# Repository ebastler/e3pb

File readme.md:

# Ender 3 (Pro) Printbed

This is an attempt of uniting print surface and heating element into a single PCB. Both heating traces and temperature sensing are located on the bottom of the PCB, while the top surface is exposed FR4 (no copper, no soldermask). 

A LED on top indicates when the heatbed is being active. Temperature sensing uses a JST XH 2-pin connector, while the heating wires can either be directly soldered, or connected with a Amass XT30U connector. Target operating voltage/power: 24V 240W.

This is a WIP and shouldn't be used just yet - I am still waiting for my Ender 3 Pro to arrive to finalize the design and order protos.

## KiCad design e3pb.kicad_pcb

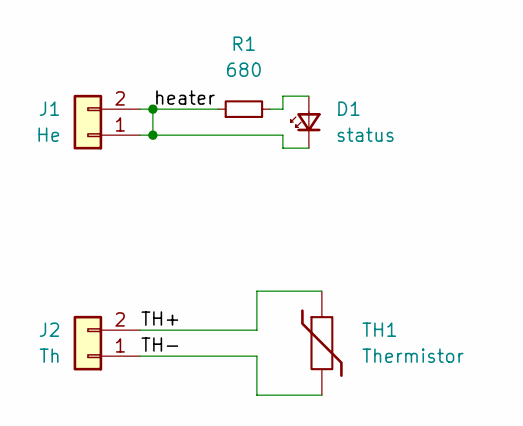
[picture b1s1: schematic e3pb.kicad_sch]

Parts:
D1: status; LED_0603_1608Metric_Pad1.05x0.95mm_HandSolder
J1: He; AMASS_XT30PW-M_1x02_P2.50mm_Horizontal
J2: Th; JST_XH_S2B-XH-A_1x02_P2.50mm_Horizontal
R1: 680; R_0603_1608Metric_Pad0.98x0.95mm_HandSolder
TH1: Thermistor; R_0603_1608Metric_Pad0.98x0.95mm_HandSolder

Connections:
/TH+: J2.2, TH1.1
/TH-: J2.1, TH1.2
/heater: D1.1 (K), J1.1, J1.2, R1.1
unnamed: D1.2 (A), R1.2

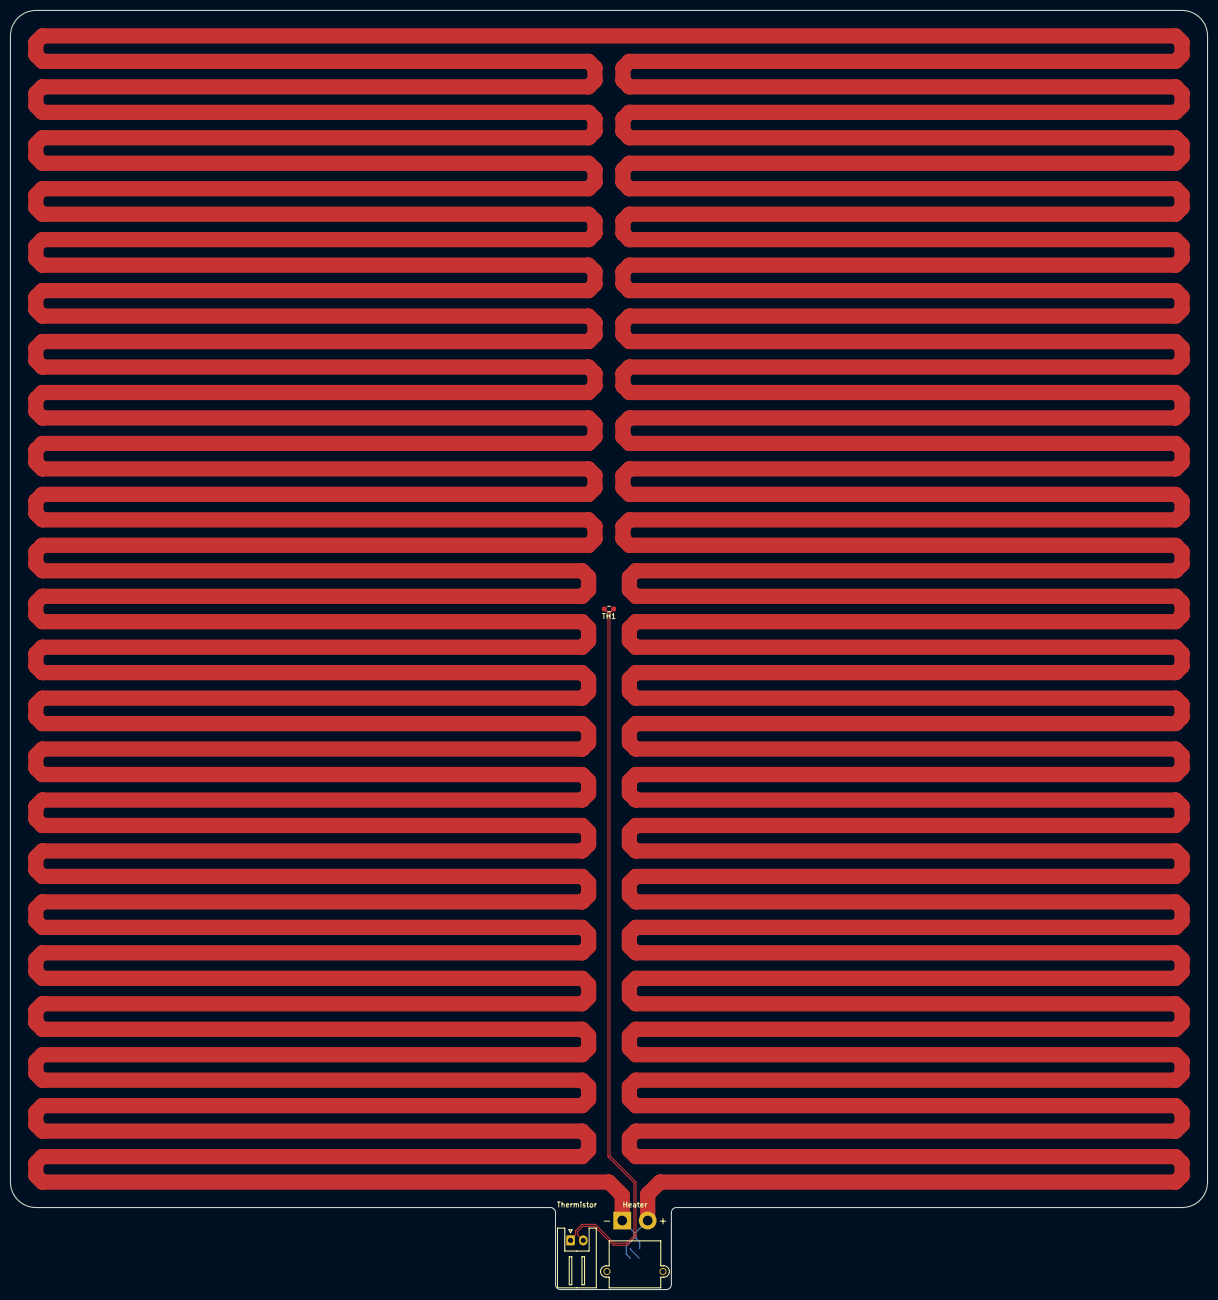
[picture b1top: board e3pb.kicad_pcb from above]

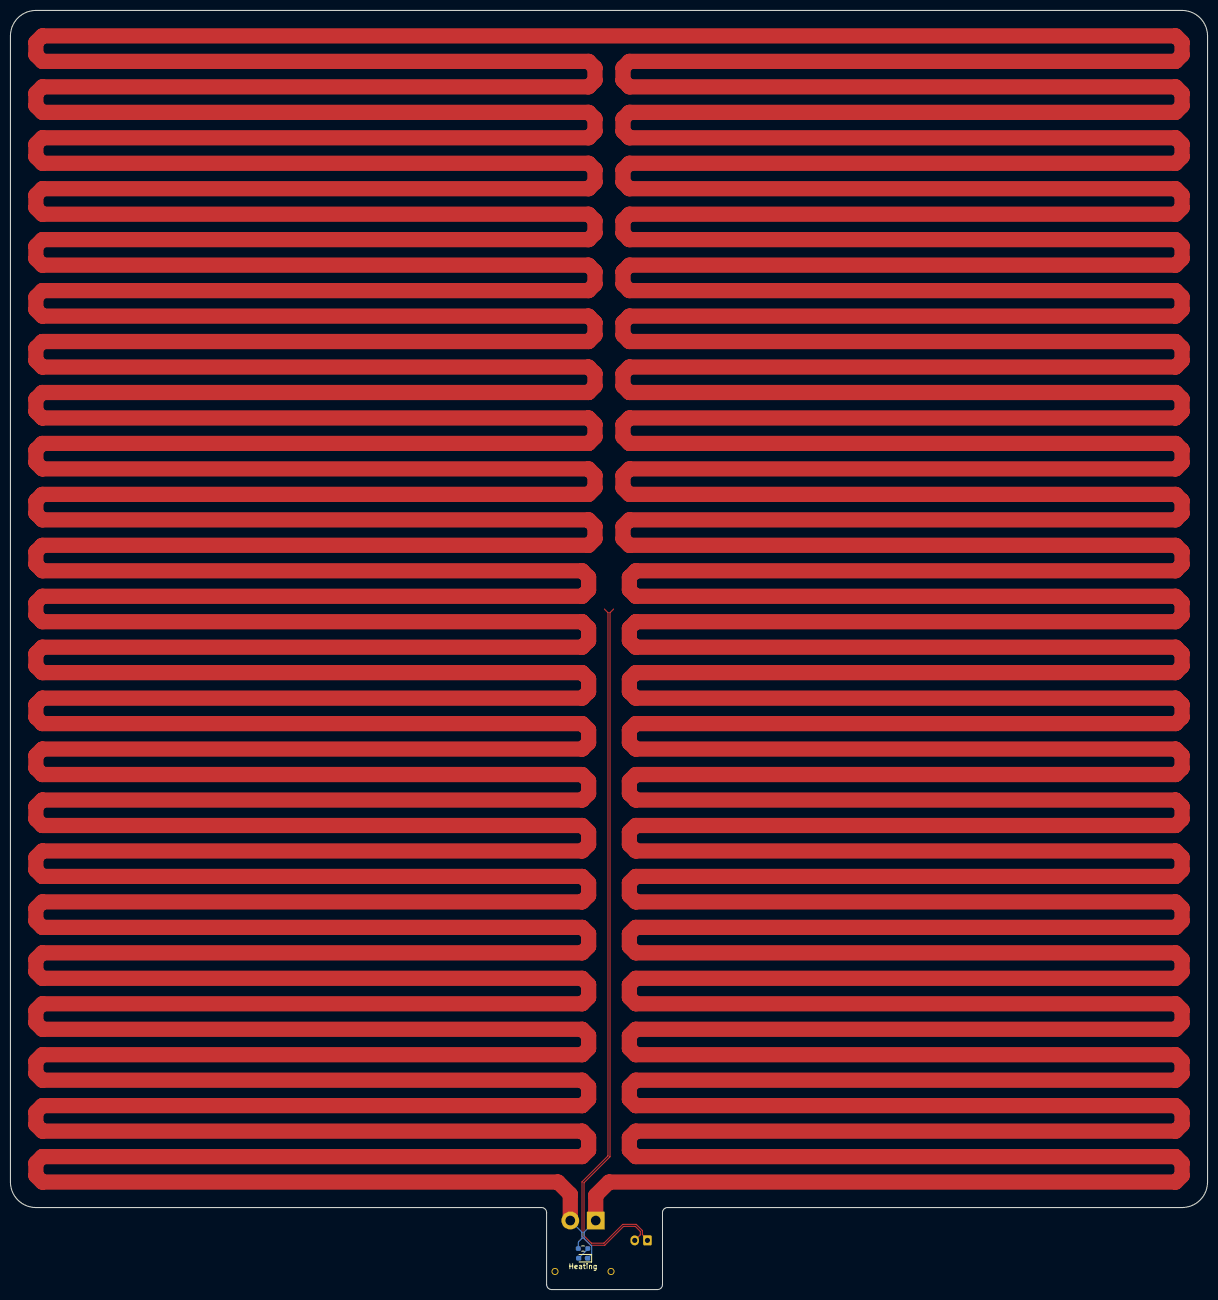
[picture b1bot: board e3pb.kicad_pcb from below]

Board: 2 copper layers, 235.0 x 251.1 mm, 5 parts (2 on the bottom side), 4 nets.
